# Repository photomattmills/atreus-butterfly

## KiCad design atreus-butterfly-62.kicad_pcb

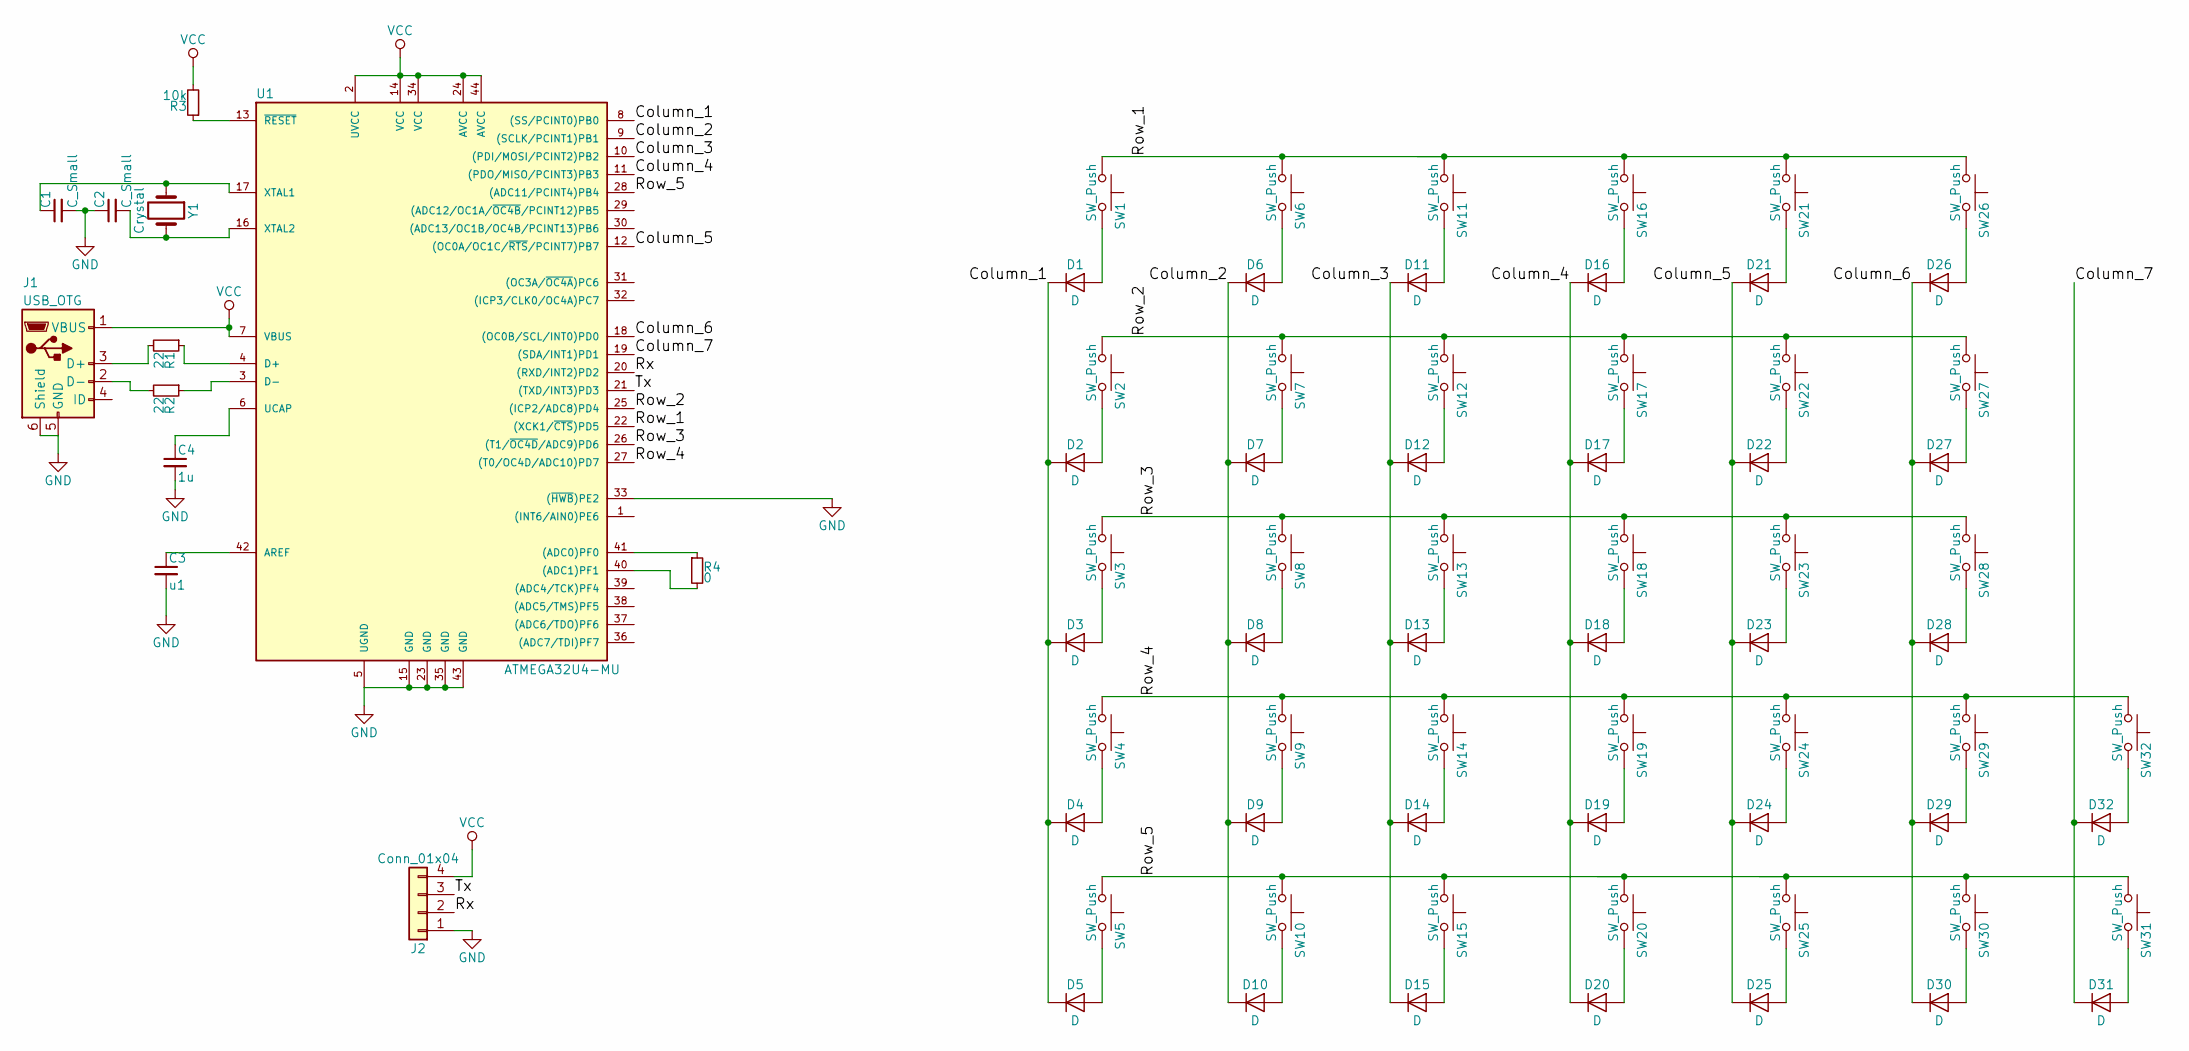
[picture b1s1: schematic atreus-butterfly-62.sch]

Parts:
C1, C2: C_Small; C_0805
C3: u1; C_0805
C4: 1u; C_0805
D1, D2, D3, D4, D5, D6, D7, D8, D9, D10, D11, D12, D13, D14, D15, D16, D17, D18, D19, D20, D21, D22, D23, D24, D25, D26, D27, D28, D29, D30, D31, D32: D; D_SOD-123
J1: USB_OTG; USB_Micro-B
J2: Conn_01x04; Pin_Header_Straight_1x04_Pitch2.54mm
R1, R2: 22; R_0603_HandSoldering
R3: 10k; R_0603_HandSoldering
R4: 0; R_0603_HandSoldering
SW1, SW2, SW3, SW4, SW5, SW6, SW7, SW8, SW9, SW10, SW11, SW12, SW13, SW14, SW15, SW16, SW17, SW18, SW19, SW20, SW21, SW22, SW23, SW24, SW25, SW26, SW27, SW28, SW29, SW30, SW31, SW32: SW_Push; Kailh_low_profile
U1: ATMEGA32U4-MU; QFN_44
Y1: Crystal; crystal_butterfly

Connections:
/Column_1: D1.1 (K), D2.1 (K), D3.1 (K), D4.1 (K), D5.1 (K), U1.8 ((SS/PCINT0)PB0)
/Column_2: D6.1 (K), D7.1 (K), D8.1 (K), D9.1 (K), D10.1 (K), U1.9 ((SCLK/PCINT1)PB1)
/Column_3: D11.1 (K), D12.1 (K), D13.1 (K), D14.1 (K), D15.1 (K), U1.10 ((PDI/MOSI/PCINT2)PB2)
/Column_4: D16.1 (K), D17.1 (K), D18.1 (K), D19.1 (K), D20.1 (K), U1.11 ((PDO/MISO/PCINT3)PB3)
/Column_5: D21.1 (K), D22.1 (K), D23.1 (K), D24.1 (K), D25.1 (K), U1.12 ((OC0A/OC1C/~RTS~/PCINT7)PB7)
/Column_6: D26.1 (K), D27.1 (K), D28.1 (K), D29.1 (K), D30.1 (K), U1.18 ((OC0B/SCL/INT0)PD0)
/Column_7: D31.1 (K), D32.1 (K), U1.19 ((SDA/INT1)PD1)
/Row_1: SW1.1, SW6.1, SW11.1, SW16.1, SW21.1, SW26.1, U1.22 ((XCK1/~CTS~)PD5)
/Row_2: SW2.1, SW7.1, SW12.1, SW17.1, SW22.1, SW27.1, U1.25 ((ICP2/ADC8)PD4)
/Row_3: SW3.1, SW8.1, SW13.1, SW18.1, SW23.1, SW28.1, U1.26 ((T1/~OC4D~/ADC9)PD6)
/Row_4: SW4.1, SW9.1, SW14.1, SW19.1, SW24.1, SW29.1, SW32.1, U1.27 ((T0/OC4D/ADC10)PD7)
/Row_5: SW5.1, SW10.1, SW15.1, SW20.1, SW25.1, SW30.1, SW31.1, U1.28 ((ADC11/PCINT4)PB4)
/Rx: J2.2, U1.20 ((RXD/INT2)PD2)
/Tx: J2.3, U1.21 ((TXD/INT3)PD3)
GND: C1.2, C2.1, C3.2, C4.2, J1.5 (GND), J1.6 (Shield), J2.1, U1.5 (UGND), U1.15 (GND), U1.23 (GND), U1.33 ((~HWB~)PE2), U1.35 (GND), U1.43 (GND), U1.45
unnamed: C1.1, U1.17 (XTAL1), Y1.1
unnamed: C2.2, U1.16 (XTAL2), Y1.2
unnamed: C3.1, U1.42 (AREF)
unnamed: C4.1, U1.6 (UCAP)
unnamed: D1.2 (A), SW1.2
unnamed: D2.2 (A), SW2.2
unnamed: D3.2 (A), SW3.2
unnamed: D4.2 (A), SW4.2
unnamed: D5.2 (A), SW5.2
unnamed: D6.2 (A), SW6.2
unnamed: D7.2 (A), SW7.2
unnamed: D8.2 (A), SW8.2
unnamed: D9.2 (A), SW9.2
unnamed: D10.2 (A), SW10.2
unnamed: D11.2 (A), SW11.2
unnamed: D12.2 (A), SW12.2
unnamed: D13.2 (A), SW13.2
unnamed: D14.2 (A), SW14.2
unnamed: D15.2 (A), SW15.2
unnamed: D16.2 (A), SW16.2
unnamed: D17.2 (A), SW17.2
unnamed: D18.2 (A), SW18.2
unnamed: D19.2 (A), SW19.2
unnamed: D20.2 (A), SW20.2
unnamed: D21.2 (A), SW21.2
unnamed: D22.2 (A), SW22.2
unnamed: D23.2 (A), SW23.2
unnamed: D24.2 (A), SW24.2
unnamed: D25.2 (A), SW25.2
unnamed: D26.2 (A), SW26.2
unnamed: D27.2 (A), SW27.2
unnamed: D28.2 (A), SW28.2
unnamed: D29.2 (A), SW29.2
unnamed: D30.2 (A), SW30.2
unnamed: D31.2 (A), SW31.2
unnamed: D32.2 (A), SW32.2
unnamed: J1.2 (D-), R2.2
unnamed: J1.3 (D+), R1.2
unnamed: R1.1, U1.4 (D+)
unnamed: R2.1, U1.3 (D-)
unnamed: R3.1, U1.13 (~RESET~)
unnamed: R4.1, U1.41 ((ADC0)PF0)
unnamed: R4.2, U1.40 ((ADC1)PF1)
VCC: J1.1 (VBUS), J2.4, R3.2, U1.2 (UVCC), U1.7 (VBUS), U1.14 (VCC), U1.24 (AVCC), U1.34 (VCC), U1.44 (AVCC)

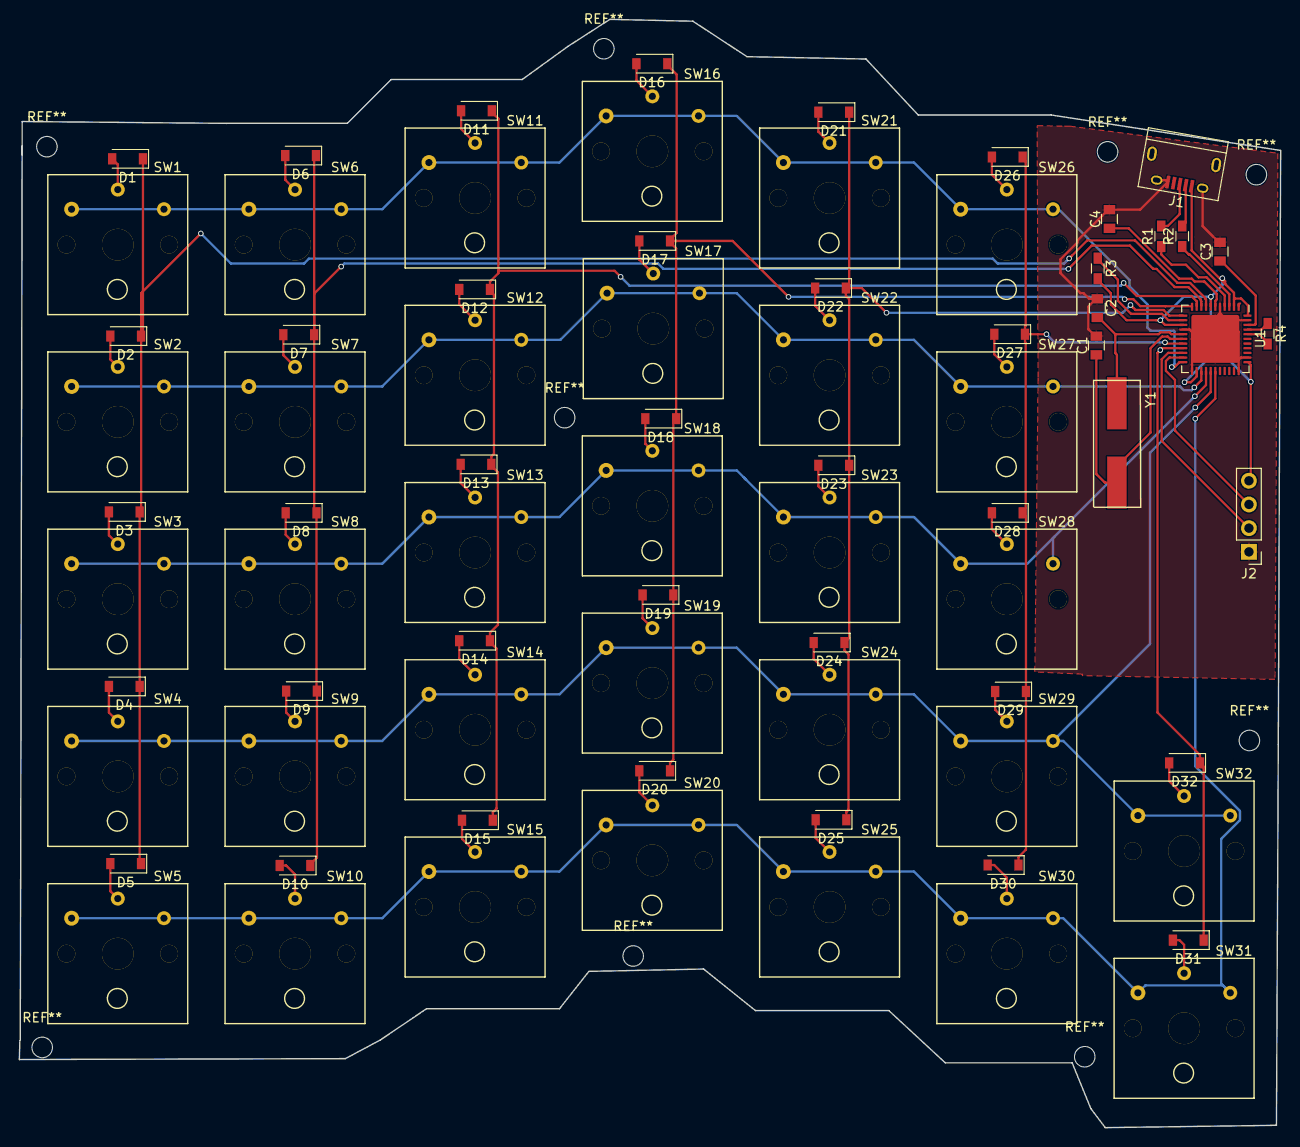
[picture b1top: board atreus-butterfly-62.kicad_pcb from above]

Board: 2 copper layers, 135.2 x 118.8 mm, 76 parts (0 on the bottom side), 59 nets.

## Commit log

2019-02-06 initial schemantic commit
2019-02-06 switch to serial comms
2019-02-25 thingy
2019-02-25 save again
2019-04-25 no middle keys
2019-04-25 add the right module for the kailh switched
2019-04-25 add correct switch footprint and fix routing
2019-05-22 more stuff done no idea really
